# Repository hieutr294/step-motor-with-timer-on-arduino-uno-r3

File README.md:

# Control 2 DRV8825 step motor driver with timer on Arduino Uno R3
This is my project with another one student to control 2 step motor 
## Requirement
- 2 DRV8825
- LCD with I2C
- Arduino Uno R3
- 2 Bipolar Step motor
## Features
- Generate pulse without using delay on Arduino Uno R3
## Tech
- This project using 2 Timer 1 and Timer 2 to generate square wave that control 2 driver of 2 step motor
- The square wave caculation like this below image

- How to generate square wave using timer please refer to ATmega datasheet and my comment inside ino file: [Datasheet](https://ww1.microchip.com/downloads/en/DeviceDoc/doc2503.pdf)
## Schematic

## Installation
You need to install LiquidCrystal_I2C library for LCD

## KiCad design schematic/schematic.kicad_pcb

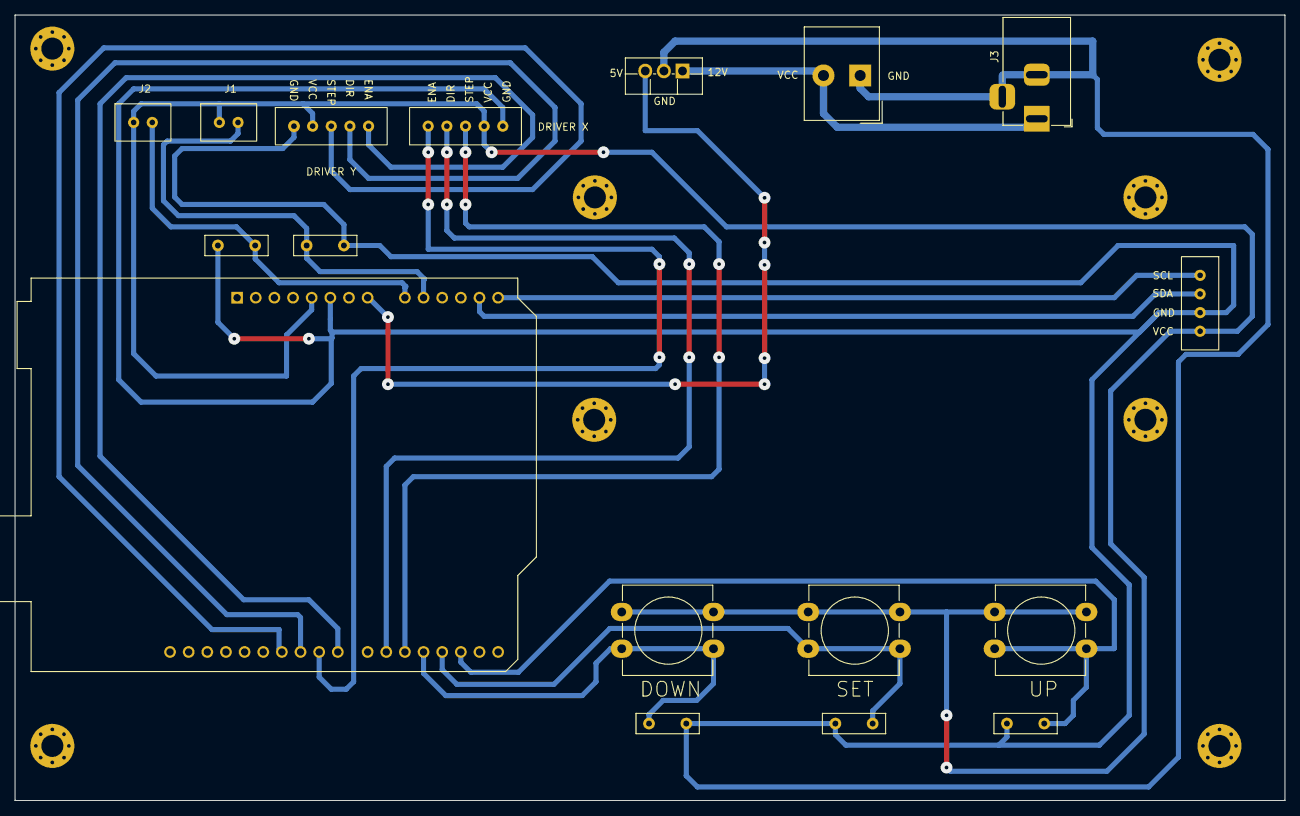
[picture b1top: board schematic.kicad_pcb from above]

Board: 2 copper layers, 173.0 x 107.0 mm, 25 parts (0 on the bottom side), 17 nets.

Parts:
A1: Arduino_UNO_R3
DOWN: SW_PUSH-12mm_Wuerth-430476085716
DRIVER X: Rao_1x5
DRIVER Y: Rao_1x5
H3, H3#2, H3#3, H3#4, H3#5, H3#6, H3#7, H3#8: MountingHole; MountingHole_3mm_Pad_Via
J1, J2: Dau_PH_1x2
J3: Barrel_Jack_Switch; BarrelJack_Horizontal
J4: Screw_Terminal_01x02; Altech_AK300_1x02_P5.00mm_45-Degree
LCD1: Rao_1x4
R1, R2, R3, R4, R5: R; R_Box_L8.4mm_W2.5mm_P5.08mm
SET: SW_PUSH-12mm_Wuerth-430476085716
U1: L7805; TO-220F-3_Vertical
UP: SW_PUSH-12mm_Wuerth-430476085716

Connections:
+5V: A1.8 (VIN), U1.3 (OUT)
/DIR_X: A1.21 (D6), DRIVER X.4
/DIR_Y: A1.25 (D10), DRIVER Y.4
/DOWN BUTTON: A1.19 (D4), DOWN.2, R2.1
/ENA_X: A1.20 (D5), DRIVER X.3
/ENA_Y: A1.23 (D8), DRIVER Y.5
/HOME_X: A1.9 (A0), J2.2, R4.1
/HOME_Y: A1.10 (A1), J1.2, R5.1
/SCL: A1.14 (SCL/A5), LCD1.1
/SDA: A1.13 (SDA/A4), LCD1.2
/SET BUTTON: A1.18 (D3), R3.1, SET.2
/STEP_X: A1.24 (D9), DRIVER X.5
/STEP_Y: A1.26 (D11), DRIVER Y.3
/UP BUTTON: A1.17 (D2), R1.1, UP.2
GND: A1.6 (GND), DRIVER X.1, DRIVER Y.1, J3.2, J3.3, J4.1, LCD1.3, R1.2, R2.2, R3.2, R4.2, R5.2, U1.2 (GND)
unnamed: J3.1, J4.2, U1.1 (IN)
VCC: A1.5 (+5V), DOWN.1, DRIVER X.2, DRIVER Y.2, J1.1, J2.1, LCD1.4, SET.1, UP.1

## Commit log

2024-01-24 inti
2024-04-11 Update README.md
    add schematic image
